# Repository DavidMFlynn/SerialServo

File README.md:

# SerialServo
Packet serial to R/C servo w/ absolute encoder
This is for one of my robot projects.
Features: TTL Serial interface, PWM output w/ 1/2 microsecond resolution, Current sensing, Absolute encoder SPI interface.
Features will be added as needed.
The Rev B PCB is being printed 6/19/2018

ToDo:

  Add params:

  Mode 4, Gripper control, closed value, open value
    Move toward close until reached or max current
    Open to open value
    OpenValue = FastRevVal, CloseValue = FastRevVal
    Speed is used for close only
    Open may be greater than or less than close, RevDirFlag?

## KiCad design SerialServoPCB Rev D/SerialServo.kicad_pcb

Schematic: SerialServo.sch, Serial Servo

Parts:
C1, C3, C4, C6, C7, C8, C11, C12, C14: 0.1uF; C_0805_2012Metric
C2: 2.2uF; CP_Radial_D5.0mm_P2.00mm
C5: 4.7uF; CP_Radial_D5.0mm_P2.00mm
C9: 220uF; CP_Radial_D8.0mm_P5.00mm
C10: 1uF; C_0805_2012Metric
D1, D2, D3, D4: LED; LED_0805_2012Metric_Pad1.15x1.40mm_HandSolder
D5, D6: SMA Diode; D_SMA
J1: Conn_01x04; Molex_KK-254_AE-6410-04A_1x04_P2.54mm_Vertical
J2: Conn_01x06; Molex_KK-254_AE-6410-06A_1x06_P2.54mm_Vertical
J3: Conn_01x05; PinHeader_1x05_P2.54mm_Vertical
J4, J5, J6, J7: Conn_01x03; Molex_KK-254_AE-6410-03A_1x03_P2.54mm_Vertical
J8: Conn_01x02; PinHeader_1x02_P2.54mm_Vertical
R1: 220R; R_0805_2012Metric
R2, R3, R7, R12, R14, R16, R18, R19, R20: 1K0; R_0805_2012Metric
R4, R9: 100K; R_0805_2012Metric
R5, R11: 10K; R_0805_2012Metric
R6: 0R200 1W; R_2512_6332Metric_Pad1.52x3.35mm_HandSolder
R8: RRR; R_0805_2012Metric
R10, R13, R15, R17: 47K; R_0805_2012Metric
R21: 120R; R_0805_2012Metric
SW1, SW2, SW3: SW_Push; SW_SPST_FSMSM
U1: PIC16F1847-ISO; SOIC-18W_7.5x11.6mm_P1.27mm
U2: LM358A; SOIC-8_3.9x4.9mm_P1.27mm
VR1: L78L05_TO92; TO-92L_Wide
VR2: LM7805_TO220; TO-263-3_TabPin2
VR3: LD1085; TO-263-3_TabPin2

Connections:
+5V: C1.1, C4.1, C14.1, J2.1, J3.2, J5.1, J6.1, J7.1, R3.2, R12.1, R13.1, R14.1, R15.1, R16.1, R17.1, U1.14, U2.8, VR1.1
+12V: D5.2 (A), D6.2 (A), J1.1, J8.1, R4.1
/AN0: C7.1, R7.2, U1.17
Batt_V: C3.1, R2.2, U1.18
ENC_CLK: J2.4, U1.10
ENC_CS: J2.3, U1.6
GND: C1.2, C2.2, C3.2, C4.2, C6.2, C7.2, C10.2, C11.2, C12.2, C14.2, J1.2, J2.2, J3.3, J5.3, J6.3, J7.3, R5.1, R6.1, R11.1, SW1.1, SW2.1, SW3.1, U1.5, U2.4, VR1.2
GNDA: C5.2, C8.2, C9.2, J4.3, R6.2, R8.2, R10.1, VR2.2 (GND)
MISO: J2.5, U1.7
MOSI: J2.6, U1.15
unnamed: C2.1, D5.1 (K), VR1.3
unnamed: C5.1, D6.1 (K), VR2.1 (VI), VR3.3
unnamed: C8.1, C9.1, J4.2, J8.2, R21.1, VR2.3 (VO), VR3.2
unnamed: C10.1, R10.2, U2.3
unnamed: D1.2 (A), R12.2
unnamed: D2.2 (A), R14.2
unnamed: D3.2 (A), R16.2
unnamed: D4.1 (K), U1.16
unnamed: D4.2 (A), R3.1
unnamed: J5.2, R18.1
unnamed: J6.2, R19.1
unnamed: J7.2, R20.1
unnamed: R1.1, U1.9
unnamed: R2.1, U2.6, U2.7
unnamed: R4.2, R5.2, U2.5
unnamed: R7.1, R9.2, U2.1
unnamed: R9.1, R11.2, U2.2
unnamed: R8.1, R21.2, VR3.1
PGC: J3.5, U1.12
PGD: J3.4, U1.13
RX: J1.4, U1.8
SW1_LED1: C11.1, D1.1 (K), R13.2, R18.2, SW1.2, U1.1
SW2_LED2: C12.1, D2.1 (K), R15.2, R19.2, SW2.2, U1.2
SW3_LED3: C6.1, D3.1 (K), R17.2, R20.2, SW3.2, U1.3
ServoPWM: J4.1, R1.2
TX: J1.3, U1.11
VPP: J3.1, U1.4

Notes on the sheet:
Vcc GND CSn CLK MISO MOSI
Power and TTL Serial
AS5047D Encoder
Prog
VPP VDD VSS PGD PGC
System LED
Optional 3A Adj. Reg.
V-Reg bypass
Note: Analog Ref+ = 5.0V
Input voltage 6.5 to 16 volts.
Optional Options
LED and Button or Switch Input or Analog Input or Digital Output
Rev. B 6/19/2018 Fixed J3 pinout, Fixed spacing of J4 to J2 to J7.
Rev. C 1/20/2019 Modified for AS5047D Encoder
Rev. D 8/29/2020 Added SW3/LED3 for home switch...
C1,C3,C4,C6,C7,C8,C11,C12 0.1uf C2 2.2uf C5 4.7uf C9 220uf C10 1.0uf
R1 220R R2,R3,R7,R12,R14,R16 R18,R19,R20 1K0 R4,R9 100K R5,R11 10K R6 0R20 R8 ?K?? Adj Volts R10,R13,R15,R17 47K R21 120R
U1 PIC16F1847 U2 LM358A

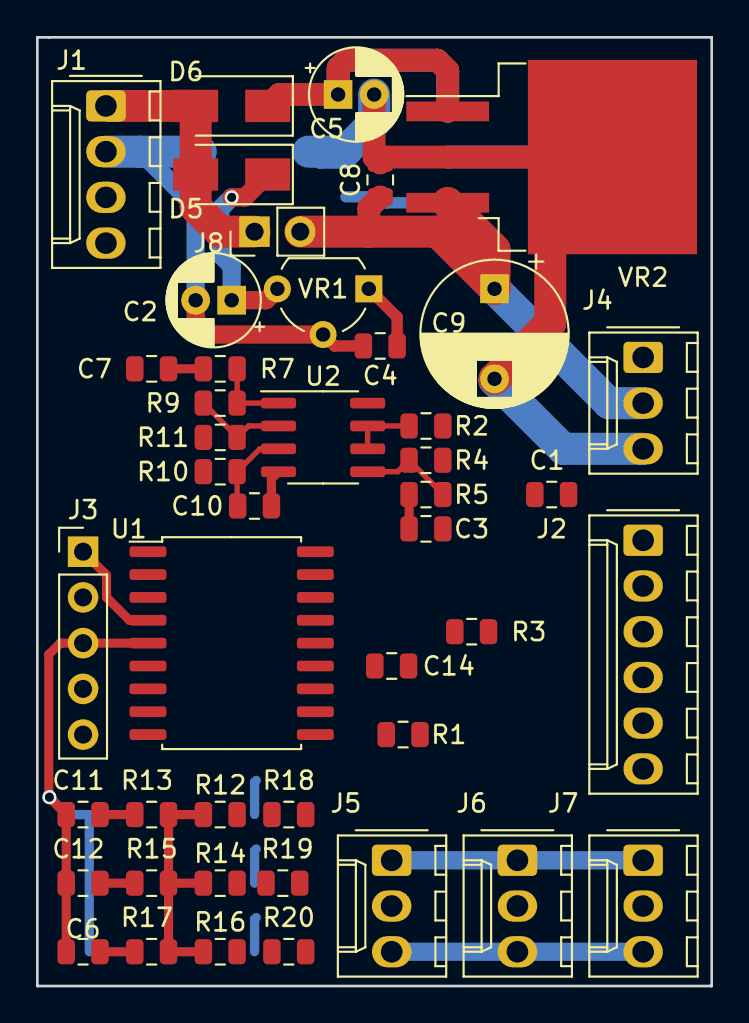
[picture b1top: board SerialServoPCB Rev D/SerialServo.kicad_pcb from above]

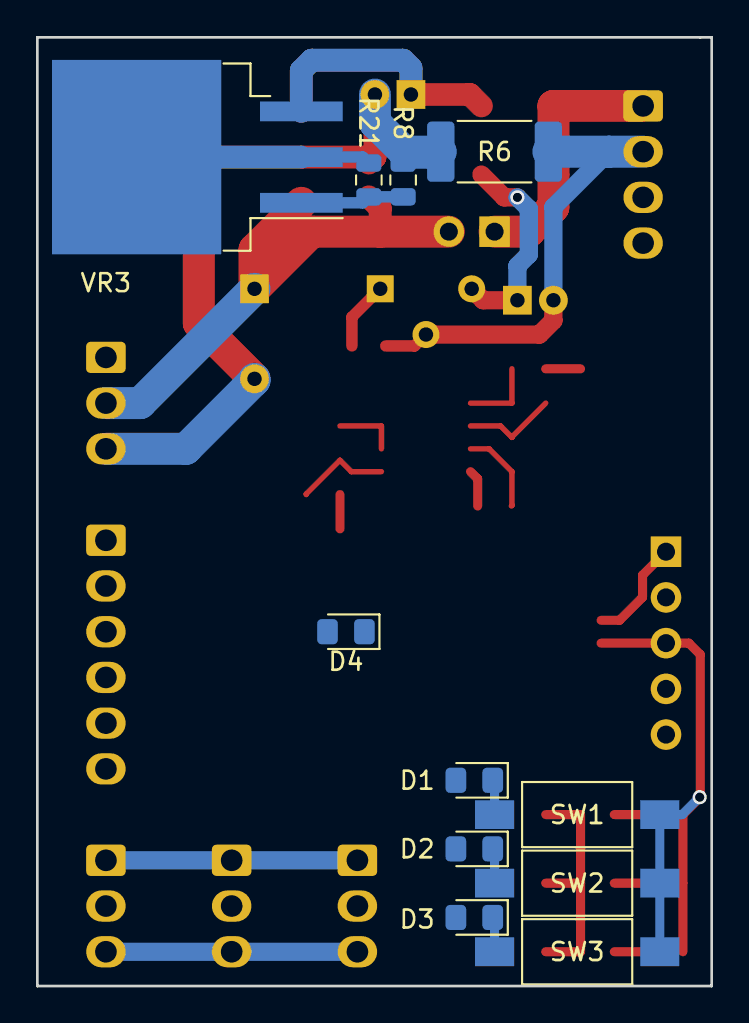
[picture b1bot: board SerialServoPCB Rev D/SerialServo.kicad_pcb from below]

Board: 2 copper layers, 37.5 x 52.7 mm, 56 parts (11 on the bottom side), 37 nets.

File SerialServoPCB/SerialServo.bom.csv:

Source,/Projects/SerialServo/SerialServoPCB/SerialServo.sch
Kicad Rev,Eeschema (5.0.0-rc2-80-gf95b77b)
Generated Date,Tuesday, June 19, 2018 at 05:32:33 PM

Title,Serial Servo
Company,DMFE
Revision,B
Date Issue,2018-06-19
Comment,TTL serial r/c servo controller

Reference,Value,Library,Library Ref
U1,PIC16F1847-ISO,MCU_Microchip_PIC16,PIC16F648A-ISO
J1,Conn_01x04,Connector_Generic,Conn_01x04
VR1,L78L05_TO92,Regulator_Linear,L78L05_TO92
VR2,LM7805_TO220,Regulator_Linear,LM7805_TO220
D5,D,Device,D
SW1,SW_Push,Switch,SW_Push
D1,LED,Device,LED
R13,47K,Device,R
R12,1K0,Device,R
C4,0.1uF,Device,C_Small
U2,LM358A,Amplifier_Operational,LM358
D6,D,Device,D
R6,0R200 1W,Device,R
C8,0.1uF,Device,C_Small
J4,Conn_01x03,Connector_Generic,Conn_01x03
R1,220R,Device,R
J3,Conn_01x05,Connector_Generic,Conn_01x05
SW2,SW_Push,Switch,SW_Push
D2,LED,Device,LED
R15,47K,Device,R
R14,1K0,Device,R
SW3,SW_Push,Switch,SW_Push
D3,LED,Device,LED
R17,47K,Device,R
R16,1K0,Device,R
C10,1uF,Device,C_Small
R10,47K,Device,R
R11,10K,Device,R
R9,100K,Device,R
R7,1K0,Device,R
C7,0.1uF,Device,C_Small
C9,100uF,Device,CP1_Small
J2,Conn_01x05,Connector_Generic,Conn_01x05
C1,0.1uF,Device,C_Small
D4,LED,Device,LED
R3,1K0,Device,R
RV1,20K,Device,R_POT
C3,0.1uF,Device,C_Small
R2,1K0,Device,R
R4,100K,Device,R
R5,10K,Device,R
C2,2.2uF,Device,CP1_Small
C5,2.2uF,Device,CP1_Small
C6,0.1uF,Device,C_Small
R21,1K0,Device,R
J5,Conn_01x03,Connector_Generic,Conn_01x03
R18,1K0,Device,R
J6,Conn_01x03,Connector_Generic,Conn_01x03
J7,Conn_01x03,Connector_Generic,Conn_01x03
R19,1K0,Device,R
C12,0.1uF,Device,C_Small
R20,1K0,Device,R
C13,0.1uF,Device,C_Small
C11,0.1uF,Device,C_Small
VR3,LD1085,Regulator_Linear,AZ1117-ADJ
J8,Conn_01x02,Connector_Generic,Conn_01x02
R22,120R,Device,R
R8,RRR,Device,R
C14,0.1uF,Device,C_Small

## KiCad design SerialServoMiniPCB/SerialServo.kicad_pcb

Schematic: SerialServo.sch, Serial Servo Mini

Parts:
C1, C3, C4, C5, C7, C8: 0.1uF; C_0805_2012Metric_Pad1.29x1.40mm_HandSolder
C2, C6: 2.2uF; CP_Radial_D5.0mm_P2.00mm
C9: 100uF; CP_Radial_D8.0mm_P5.00mm
C10: 1uF; C_0805_2012Metric_Pad1.29x1.40mm_HandSolder
D1, D3: D; D_SMA_Handsoldering
D2: LED; LED_0805_2012Metric_Pad1.12x1.40mm_HandSolder
J1: Conn_01x04; Molex_KK-254_AE-6410-04A_1x04_P2.54mm_Vertical
J2: Conn_01x05; Molex_KK-254_AE-6410-05A_1x05_P2.54mm_Vertical
J3: Conn_01x05; PinHeader_1x05_P2.54mm_Vertical
J4: Conn_01x03; Molex_KK-254_AE-6410-03A_1x03_P2.54mm_Vertical
R1: 220R; R_0805_2012Metric_Pad1.29x1.40mm_HandSolder
R2, R3, R7: 1K0; R_0805_2012Metric_Pad1.29x1.40mm_HandSolder
R4, R8: 100K; R_0805_2012Metric_Pad1.29x1.40mm_HandSolder
R5, R10: 10K; R_0805_2012Metric_Pad1.29x1.40mm_HandSolder
R6: 0R200 1W; R_2512_6332Metric_Pad1.49x3.40mm_HandSolder
R9: 47K; R_0805_2012Metric_Pad1.29x1.40mm_HandSolder
U1: PIC16F1847-ISO; SOIC-18W_7.5x11.6mm_P1.27mm
U2: LM358A; SOIC-8_3.9x4.9mm_P1.27mm
VR1: L78L05_TO92; TO-92L_Wide
VR2: LM7805_TO220; TO-263-3_TabPin2

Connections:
+5V: C1.1, C4.1, C5.1, J2.1, J3.2, R3.2, U1.14 (VDD), U2.8 (V+), VR1.1 (VO)
+12V: D1.2, D3.2, J1.1, R4.1
/AN0: C7.1, R7.2, U1.17 (AN0/RA0)
Batt_V: C3.1, R2.2, U1.11 (RB5)
ENC_CLK: J2.4, U1.10 (RB4/PGM)
ENC_CS: J2.2, U1.6 (RB0/INT)
Enc_DO: J2.5, U1.15 (CLKOUT/OSC2/RA6)
GND: C1.2, C2.2, C3.2, C4.2, C5.2, C7.2, C10.2, J1.2, J2.3, J3.3, R5.1, R6.1, R10.1, U1.5 (VSS), U2.4 (V-), VR1.2 (GND)
GNDA: C6.2, C8.2, C9.2, J4.3, R6.2, R9.1, VR2.2
unnamed: C2.1, D1.1, VR1.3 (VI)
unnamed: C6.1, D3.1, VR2.1
unnamed: C8.1, C9.1, J4.2, VR2.3
unnamed: C10.1, R9.2, U2.3 (+)
unnamed: D2.1, U1.16 (CLKIN/OSC1/RA7)
unnamed: D2.2, R3.1
unnamed: R1.1, U1.9 (RB3/CCP1)
unnamed: R2.1, U2.6 (-), U2.7
unnamed: R4.2, R5.2, U2.5 (+)
unnamed: R7.1, R8.2, U2.1
unnamed: R8.1, R10.2, U2.2 (-)
PGC: J3.5, U1.12 (RB6/T1OSC0/T1CKI/PGC)
PGD: J3.4, U1.13 (RB7/T1OSI/PGD)
RX: J1.4, U1.7 (RB1/RX/DT)
ServoPWM: J4.1, R1.2
TX: J1.3, U1.8 (RB2/TX/CK)
VPP: J3.1, U1.4 (~MCLR~/Vpp/RA5)

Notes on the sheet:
Prog
VDD VPP VSS PGD PGC
Encoder
VDD CS* VSS CLK DO
System LED
Note: Analog Ref+ = 5.0V
Input voltage 6.5 to 16 volts.
Rev. B 6/19/2018 Fixed J3 pinout, Fixed spacing of J4 to J2 to J7.
Power and TTL Serial
Mini n/c 6/21/2018 Removed stuff.

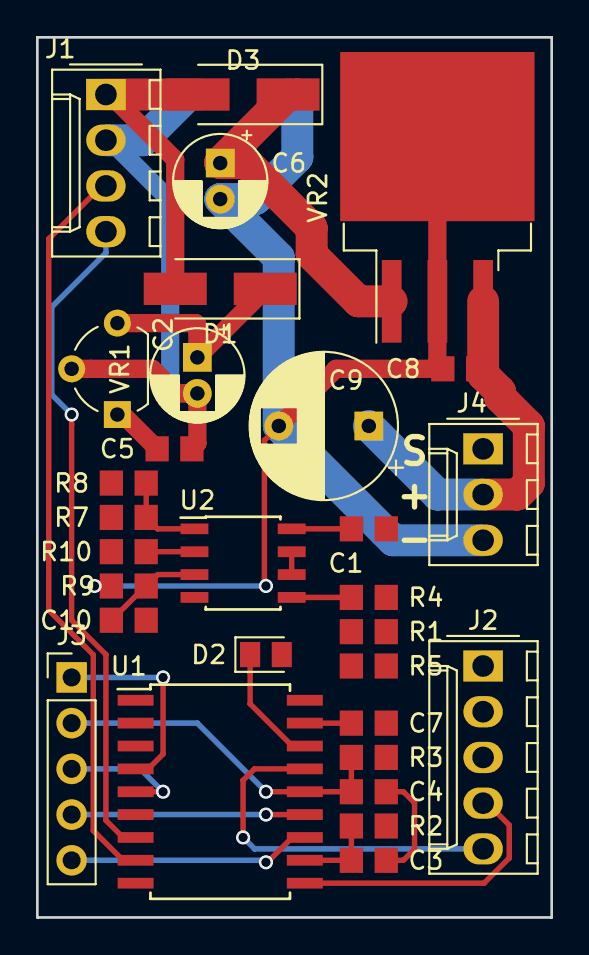
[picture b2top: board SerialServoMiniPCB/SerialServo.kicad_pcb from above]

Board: 2 copper layers, 28.6 x 48.9 mm, 31 parts (1 on the bottom side), 26 nets.

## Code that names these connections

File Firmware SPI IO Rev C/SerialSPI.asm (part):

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;   Pin 1 (RA2/AN2)                           SW1/LED1 (Active Low Input/Output)
;   Pin 2 (RA3/AN3)                           SW2/LED2 (Active Low Input/Output)
;   Pin 3 (RA4/AN4)                           n/c
;   Pin 4 (RA5/MCLR*)                         VPP/MCLR*
;   Pin 5 (GND)                               Ground
;   Pin 6 (RB0)                               SPI CSBit (Active Low Output)
;   Pin 7 (RB1/AN11/SDA1)                     SPI MISO (Digital Input)
;   Pin 8 (RB2/AN10/TX)                       TTL Serial RX
;   Pin 9 (RB3/CCP1)                          Pulse output for Servo
;
;   Pin 10 (RB4/AN8/SLC1)                     SPI SCL1
;   Pin 11 (RB5/AN7)                          TTL Serial TX
;   Pin 12 (RB6/AN5/CCP2)                     ICSPCLK
;   Pin 13 (RB7/AN6)                          ICSPDAT
;   Pin 14 (Vcc)                              +5 volts
;   Pin 15 (RA6)                              SPI MOSI (Digital Output)
;   Pin 16 (RA7/CCP2)                         LED3 (Active Low Output)(System LED)
;   Pin 17 (RA0/AN0)                          Current sensing analog input
;   Pin 18 (RA1/AN1)                          Battery voltage sensing analog input
;
;====================================================================================================
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; INTOSC oscillator: I/O function on CLKIN pin
; WDT disabled
; PWRT disabled
; MCLR/VPP pin function is digital input
; Program memory code protection is disabled
; Data memory code protection is disabled
; Brown-out Reset enabled
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#Define	SW1_In	PORTA,2	;SW1/LED1
#Define	SW2_In	PORTA,3	;SW2/LED2
#Define	RA4_In	PORTA,4	;n/c
#Define	RA5_In	PORTA,5	;VPP/MCLR*
#Define	RA6_Out	PORTA,6	;MagEnc_DataBit Encoder MOSI (SPI, Digital Output)
#Define	RA7_In	PORTA,7	;LED3 (Active Low Output)(System LED)
LED1_Bit	EQU	2	;LED1 (Active Low Output)
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
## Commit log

2018-04-27 Just getting started
2018-05-01 Gripper
2018-05-03 Started PCB
2018-05-05 Schematic 1.0
2018-05-06 PCB ordered
2018-05-14 working on blink
2018-05-14 Blink
2018-05-15 it blinks
2018-05-16 mode 1
2018-05-17 more test code
2018-05-17 it assembles
2018-05-18 commands
2018-05-19 Testing program
2018-05-19 beginning to work
2018-05-20 Got Serial?
2018-05-23 Serial...
2018-05-24 works once?
2018-05-24 parse fail
2018-05-25 it begins to do something
2018-05-25 new commands
2018-05-26 more commands and testing
2018-05-27 testing continues
    Works as single servo position control.
2018-05-27 a few more commands
2018-05-29 Mode 2 mostly working
2018-05-29 bug fixes
2018-05-30 Modes 2 and 3 mow working
2018-05-31 notes
2018-05-31 more settings
2018-06-01 1.0a3
    Getting close to feature complete, Speed has a bug.
2018-06-01 compiled binaries
2018-06-02 Mode 2 is working.
2018-06-02 This is Beta One
    Modes 2 and 3 work. No current limit yet.
2018-06-02 Current in mode 2
2018-06-03 Sync bytes enabled
2018-06-04 Tested w/ 2 servos on the same UART
2018-06-04 PCb Rev A
2018-06-05 ID String
2018-06-06 PCB Rev A work
2018-06-06 more lines
2018-06-06 Rev A PCB is ordered
2018-06-08 encoder cable
2018-06-08 current limit in mode3
2018-06-09 moved RS232 stuff to bank 1
2018-06-09 making room
2018-06-09 Works good
    This rev is good enough for now.
2018-06-10 Copy and Paste
    Added copy and paste of params between units to make setup easy.
2018-06-13 sneeking up on a robot arm controller
2018-06-16 code cleanup
2018-06-19 wRobotTest
2018-06-20 PCB Rev B
2018-06-20 Fast 10mS PWM enabled
2018-06-22 Started mini pcb
2018-07-10 more docs
2018-07-11 began adding gripper
2018-07-11 fixed order
2018-07-14 grip no work
2018-07-14 works now
2018-07-16 UI cleaning
2018-07-18 Aux IO
2018-07-19 refactor to class
2018-07-20 for Roger
2018-07-20 mode read
2018-07-23 multiservo
2018-07-25 multi-servo tests
2018-07-25 lo rez
2018-08-06 added open, save, save as
2018-08-13 Tube mounted case for rev B
2018-08-18 neeter
2018-08-18 Mode 3 offset
2018-08-19 little things
2018-08-19 box fix
2018-08-22 Encoder offset in Mode 3
2018-10-02 1200bard
2018-10-02 ignor
2018-10-02 time
2018-10-03 HiZ Tx fixed
    added diode, not doable in s/w
2018-10-03 mode 3 works!
2018-10-05 corner control test
2018-10-05 working a little
2018-10-05 crab
2018-12-28 Update ignore
2019-01-20 PCB Rev C Schmatic
2019-02-17 ordered rev C
2019-02-25 merged with Enc1 Prog
2019-03-01 merging Brushed servo
2019-03-02 merged serial brushed
2019-03-06 getting close, added find
2019-03-16 Rename
2019-03-19 work on SIM
2019-03-21 more sim
2019-03-22 Start Rev C firmware
    w/ BootLoader
2019-03-23 more work on bootloader
2019-03-23 New Rev C works
    except for the bootloader
2019-03-24 worked on SIM
2019-03-30 little fix
2019-04-07 Bootloader working
2019-04-28 TJoy test
2019-04-28 Comp
2019-04-28 TJoy work
2019-05-03 refactor serial ports
2019-05-12 multi-serial
2019-06-10 TJoy and Multi Serial
2019-06-11 MrBlue w/ TJoy
2019-07-28 Updated binary
2019-07-30 Fractional speed brushed servo
2019-07-30 new bin
2019-08-05 Added URanger
2019-08-06 URanger Auto Trigger
2019-08-11 works on Pi
2019-08-11 Updates for Rev C PCB
2019-08-19 Server test successful
2019-08-19 TCP tester added
2019-08-21 threads?
2019-08-22 Thread fix
2019-08-23 Tracks Demo
2019-08-24 Tracks is stopping at range
2019-08-25 TJoy and Tracks Thread
2019-08-27 Good T-Joy
2019-08-27 Automatic serial port opener
2019-08-30 Wall Bumper mode
2019-08-30 worked on wall bumper
2019-09-01 Wall Bumping
2019-09-01 Wall bumper is working on the pi
2019-09-02 Added Lidar-Lite calc to URanger
2019-09-03 MrBlue...
2019-09-04 more J
2019-09-04 more joy, getting closer
2019-09-06 we have joy!
2019-09-06 better command communications
2019-09-21 Fixed Enc1Prog port select
2019-09-21 Thinking X2
2019-09-21 Port index fix
2019-09-22 worked on X2
2019-10-12 Xojo 2019r2 update begins
2019-10-13 De-Depricating
2019-10-14 updating...
2019-10-15 needs testing
2019-10-16 no serial...
2019-11-13 revert to old
2019-11-24 serial?
2019-11-27 serial working
2019-12-15 xojo2019r3
2019-12-15 no text encoding!
2020-03-03 moving to MacroPIC + BLDC
2020-03-09 cleanup
2020-03-15 Added BLDC drive
2020-03-22 BLDC Servo working
2020-03-24 BLDC stats
2020-03-25 Aux Config and BLDC Servo
2020-03-28 BLDC Servo Acceleration added
2020-03-29 Work on BLDC
2020-03-29 Mr Blue tester updated
2020-03-31 Brushed UI updates
2020-04-07 updated bootloader
    began adding PID
2020-04-10 Improved mode 3
2020-04-14 End stops
2020-04-18 Added QEI config window
2020-04-19 Packet serial to SPI
2020-04-19 SPI doesn't validate
2020-04-19 Got RX?
2020-04-19 SPI to TMC4361A working
2020-04-19 Reading and writing SPI by address in hex
2020-04-21 started tmc4361 io
2020-04-22 TMC code
2020-04-25 had bad motion
2020-04-25 arrrg
2020-04-28 motion test
2020-05-01 Events window
2020-05-02 Status window
2020-05-03 moving
2020-07-30 ignore
2020-08-25 Working on PID
2020-08-26 Updated Command Dispatcher
2020-08-27 ClampInt bug fixed
2020-08-28 Push C changes back to B for Mr Blue
2020-08-30 Rev D PCB
2020-08-30 Aux IO and AN updates
2020-08-31 Aux N init
2020-10-17 Worked on brushed motor
2021-04-02 just
2021-04-03 adding SSC16PS
2021-04-03 worked on SSC16
2021-04-04 worked on Simple Servo 16
2021-04-06 work on SSC16
2021-04-13 SSC16 update
2021-04-15 SSC16 Sequencer tested
2021-04-16 work on sequence editor
2021-04-18 more sequencer
2021-04-20 SSC16 Sequencer is working
2021-04-21 BLDC Zero
2021-06-15 Added TSMT folder and notes
2021-07-11 notes and invert home
2021-07-16 worked on BLDC tester
2022-01-18 small update
